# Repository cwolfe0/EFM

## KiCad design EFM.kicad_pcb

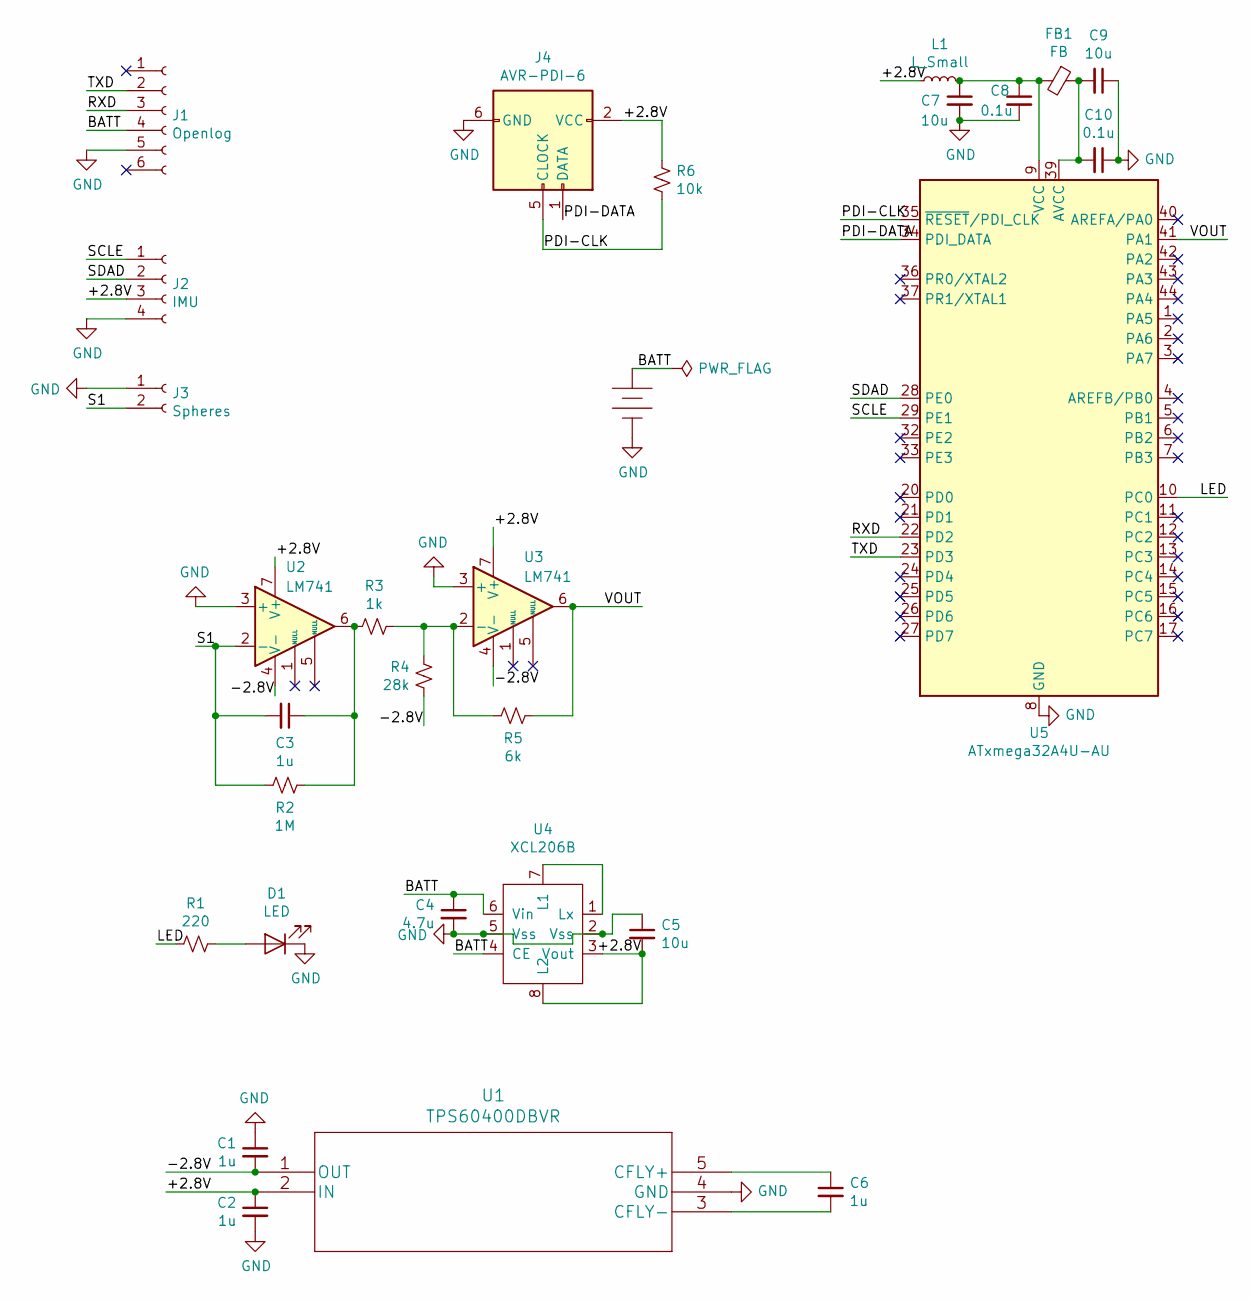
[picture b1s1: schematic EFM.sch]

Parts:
C1, C2, C3, C6: 1u; C_0805_2012Metric_Pad1.15x1.40mm_HandSolder
C4: 4.7u; C_0805_2012Metric_Pad1.15x1.40mm_HandSolder
C5, C7, C9: 10u; C_0805_2012Metric_Pad1.15x1.40mm_HandSolder
C8, C10: 0.1u; C_0805_2012Metric_Pad1.15x1.40mm_HandSolder
D1: LED; LED_0805_2012Metric
FB1: FB; L_0805_2012Metric_Pad1.15x1.40mm_HandSolder
J1: Openlog; Molex_KK-254_AE-6410-06A_1x06_P2.54mm_Vertical
J2: IMU; Molex_KK-254_AE-6410-04A_1x04_P2.54mm_Vertical
J3: Spheres; Molex_KK-254_AE-6410-02A_1x02_P2.54mm_Vertical
J4: AVR-PDI-6; PinHeader_2x03_P2.54mm_Vertical
L1: L_Small; L_0805_2012Metric_Pad1.15x1.40mm_HandSolder
M1: SHC_123_BATTERY_HOLDERCR-123-A; SHC_CR-123-A_HOLDER
R1: 220; R_0805_2012Metric_Pad1.15x1.40mm_HandSolder
R2: 1M; R_0805_2012Metric_Pad1.15x1.40mm_HandSolder
R3: 1k; R_0805_2012Metric_Pad1.15x1.40mm_HandSolder
R4: 28k; R_0805_2012Metric_Pad1.15x1.40mm_HandSolder
R5: 6k; R_0805_2012Metric_Pad1.15x1.40mm_HandSolder
R6: 10k; R_0805_2012Metric_Pad1.15x1.40mm_HandSolder
U1: TPS60400DBVR
U2, U3: LM741; SOIC-8_3.9x4.9mm_P1.27mm
U4: XCL206B; 6-TDFN
U5: ATxmega32A4U-AU; TQFP-44_10x10mm_P0.8mm

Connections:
/+2.8V: C2.1, C5.2, J2.3, J4.2 (VCC), L1.1, R6.1, U1.2 (IN), U2.7 (V+), U3.7 (V+), U4.3 (Vout), U4.8 (L2)
/-2.8V: C1.2, R4.2, U1.1 (OUT), U2.4 (V-), U3.4 (V-)
/BATT: C4.1, J1.4, M1.+, U4.4 (CE), U4.6 (Vin)
/LED: R1.2, U5.10 (PC0)
/PDI-CLK: J4.5 (CLOCK), R6.2, U5.35 (~RESET~/PDI_CLK)
/PDI-DATA: J4.1 (DATA), U5.34 (PDI_DATA)
/RXD: J1.3, U5.22 (PD2)
/S1: C3.2, J3.2, R2.2, U2.2 (-)
/SCLE: J2.1, U5.29 (PE1)
/SDAD: J2.2, U5.28 (PE0)
/TXD: J1.2, U5.23 (PD3)
/VOUT: R5.1, U3.6, U5.41 (PA1)
GND: C1.1, C2.2, C4.2, C5.1, C7.2, C8.2, C9.1, C10.1, D1.1 (K), J1.5, J2.4, J3.1, J4.6 (GND), M1.-, U1.4 (GND), U2.3 (+), U3.3 (+), U4.2 (Vss), U4.5 (Vss), U5.8 (GND), U5.18 (GND), U5.30 (GND), U5.38 (GND)
unnamed: C3.1, R2.1, R3.2, U2.6
unnamed: C6.1, U1.5 (CFLY+)
unnamed: C6.2, U1.3 (CFLY-)
unnamed: C7.1, C8.1, FB1.2, L1.2, U5.9 (VCC), U5.19 (VCC), U5.31 (VCC)
unnamed: C9.2, C10.2, FB1.1, U5.39 (AVCC)
unnamed: D1.2 (A), R1.1
unnamed: R3.1, R4.1, R5.2, U3.2 (-)
unnamed: U4.1 (Lx), U4.7 (L1)

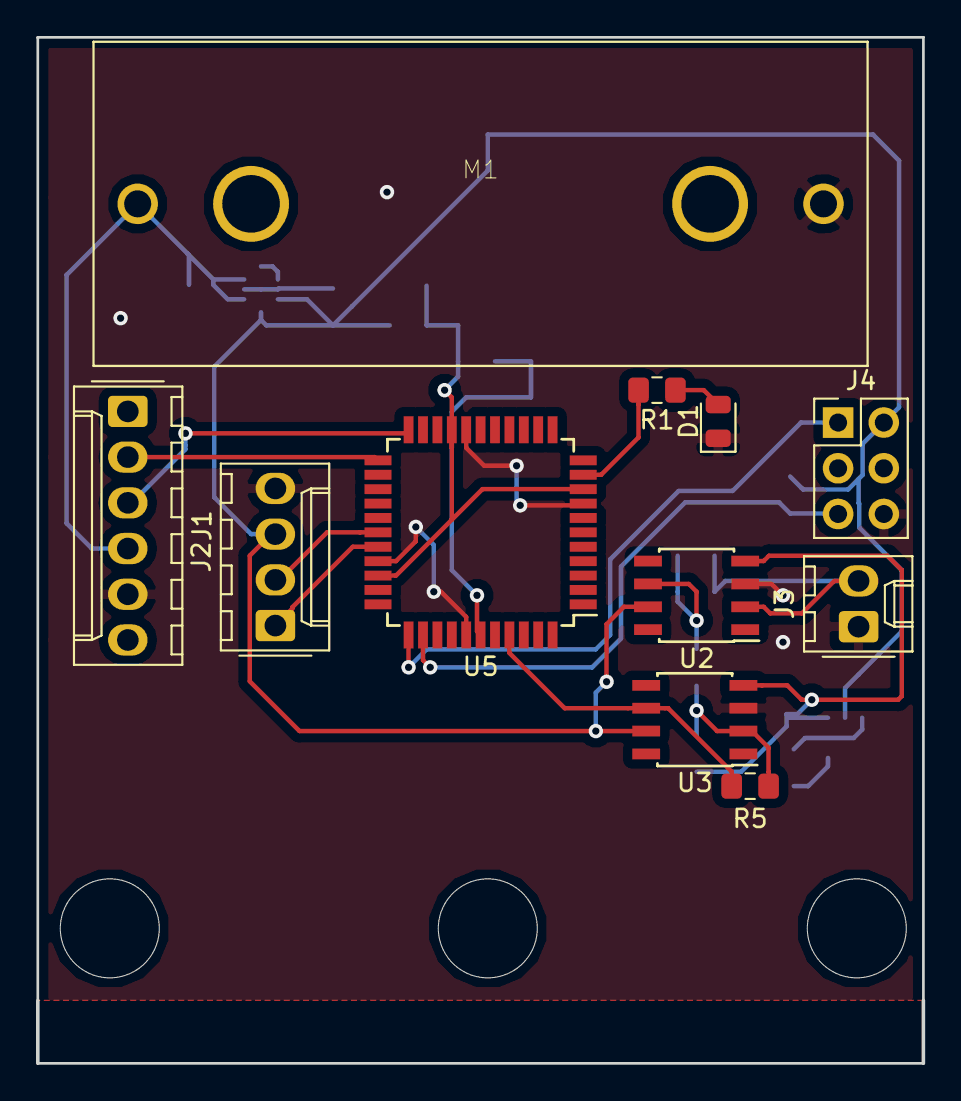
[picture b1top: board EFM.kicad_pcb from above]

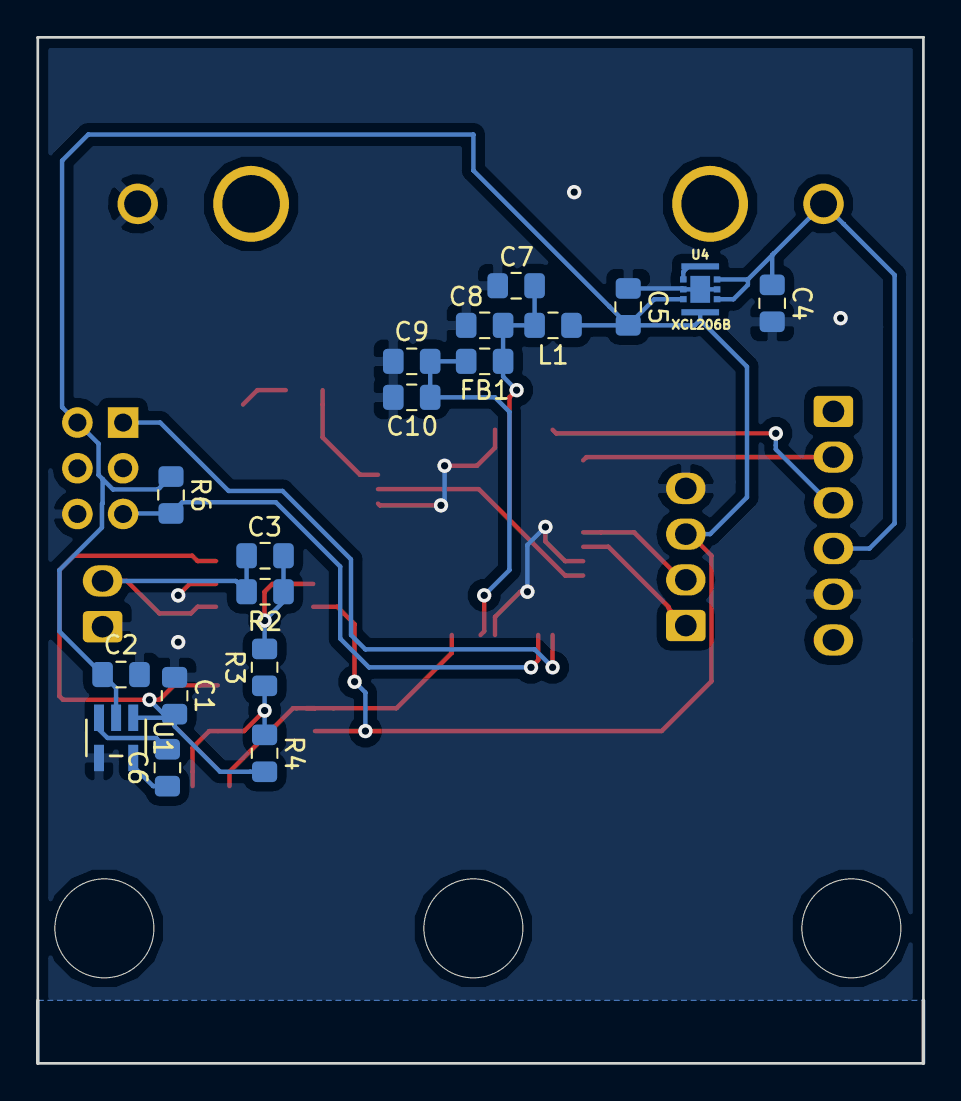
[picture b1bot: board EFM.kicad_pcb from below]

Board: 2 copper layers, 49.2 x 57.0 mm, 29 parts (18 on the bottom side), 21 nets.

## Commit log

2018-02-18 fixing stuff
2018-02-20 fix op-amp connections
2018-02-20 fix naming convention
2018-02-26 Added HELEN logo and musical imagery as tax
2018-02-26 add gerber zip for OSHPark
2018-02-26 Changing logo stuff, added gerber zip
2018-10-17 Make fixes, remove XBEE, add screw holes
2018-10-17 cleanup
2018-10-17 not 100% sure what changed, hopefully not much
2018-10-18 Remake Gerbers for updated design
2018-10-18 Fix component being under other component, remake Gerbers
2018-10-19 Add dimensions for drills
2019-02-02 delet this
2019-02-02 delet this too
2019-02-02 Update gerbers, board frigged up so the eagle board isn't accurate/not functional
2019-02-12 Move to KiCAD, add 2.8V regulator and make op-amp output to MCU >0V
2019-02-12 Add readme
2019-02-12 Add silkscreen logos/info and add render
2019-02-22 Small updates
2019-02-22 Add dimensions for mounting holes

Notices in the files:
parts and their libraries:
Copyright 2016 Accelerated Designs. All rights reserved.
